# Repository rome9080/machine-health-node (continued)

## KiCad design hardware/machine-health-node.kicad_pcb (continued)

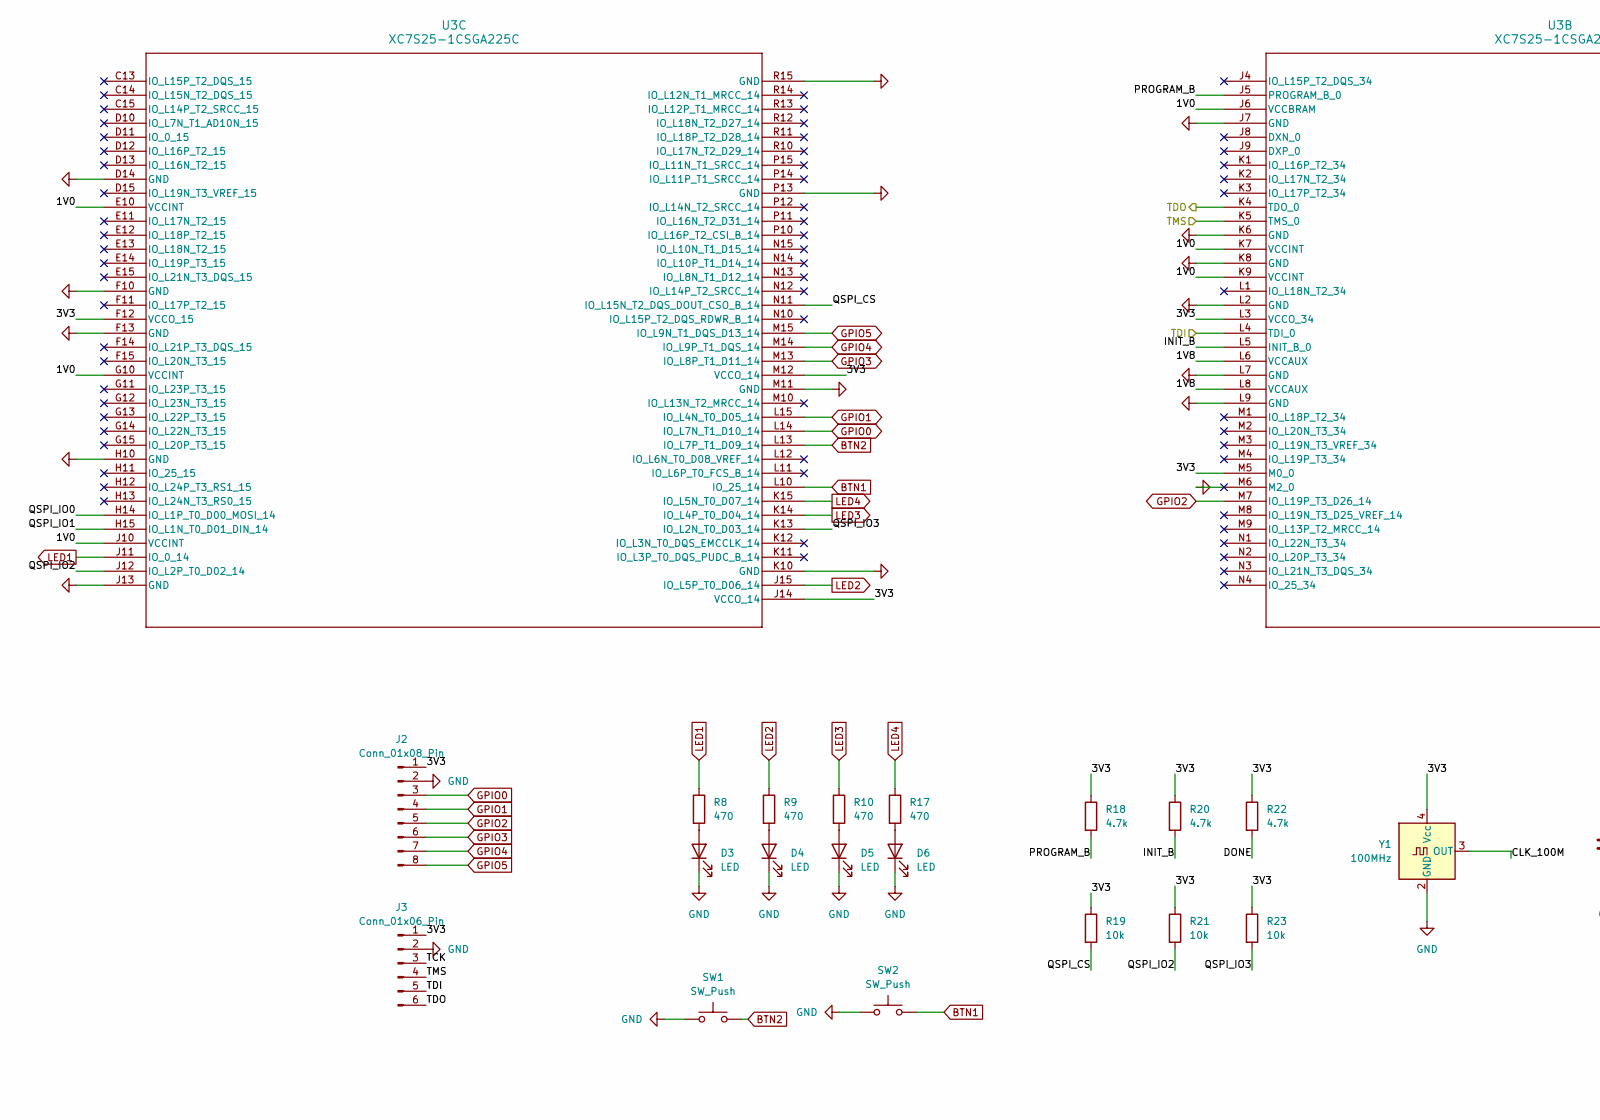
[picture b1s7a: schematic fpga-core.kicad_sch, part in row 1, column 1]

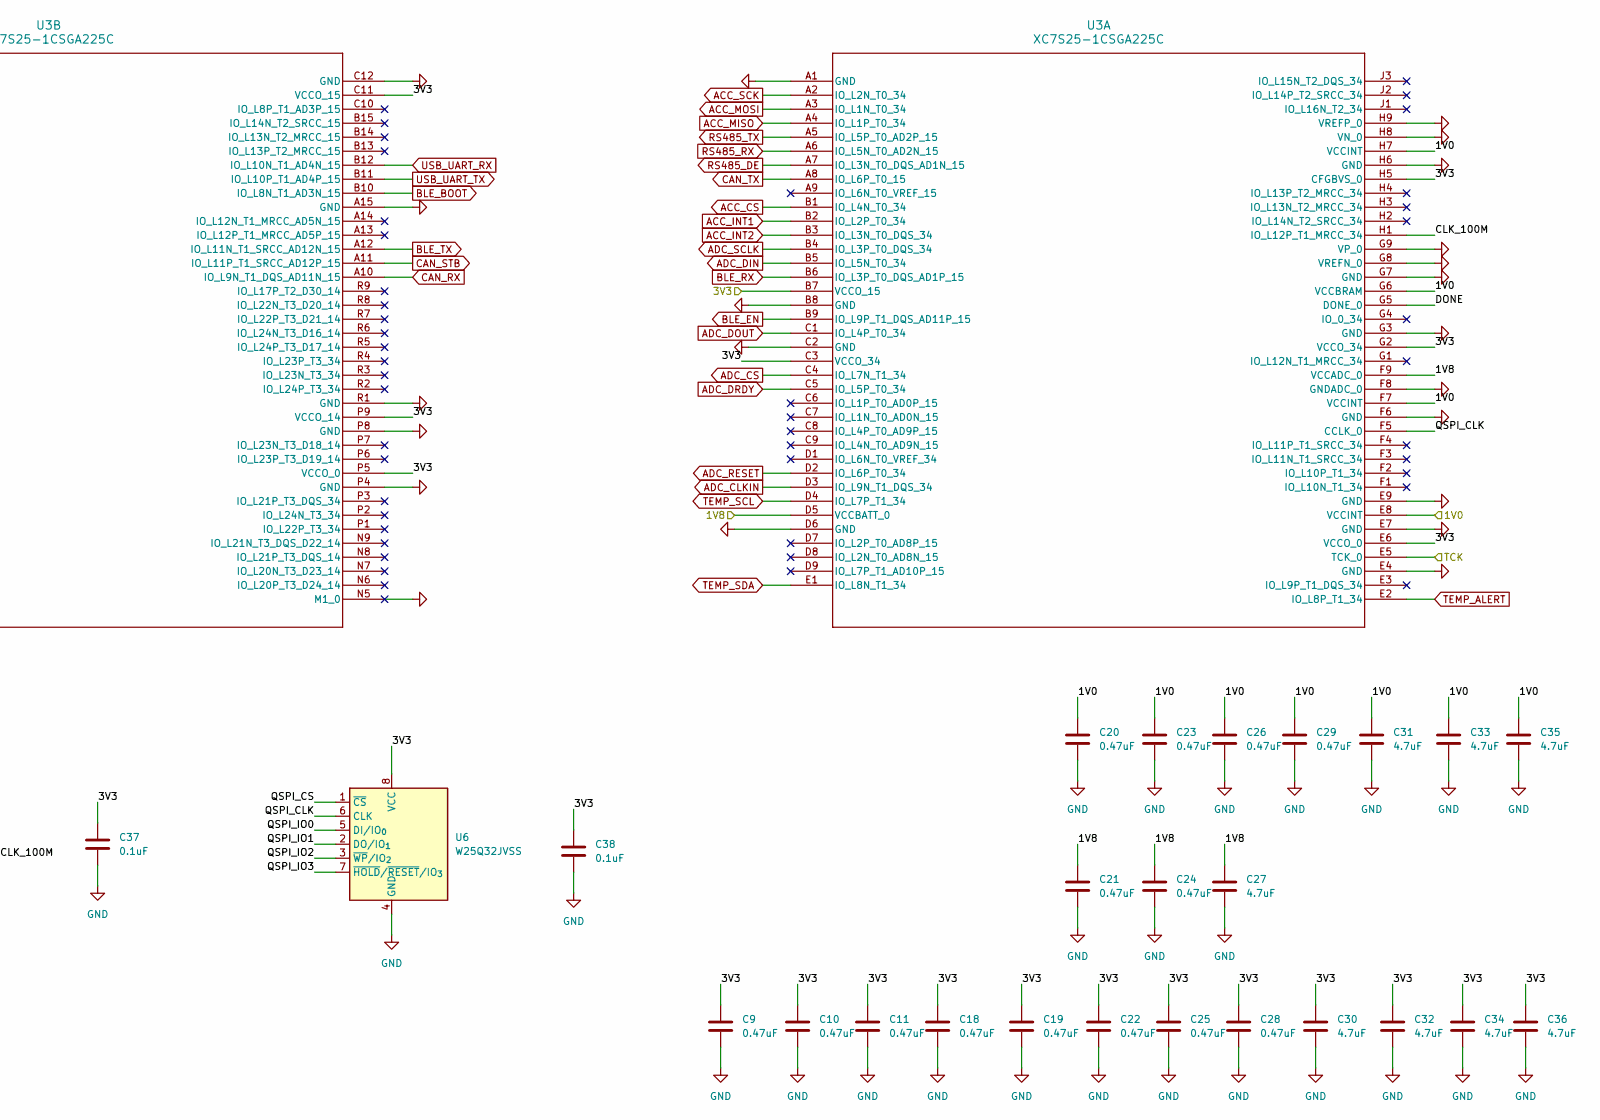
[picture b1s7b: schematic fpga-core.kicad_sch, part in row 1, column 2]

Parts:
C9, C10, C11, C18, C19, C20, C21, C22, C23, C24, C25, C26, C28, C29: 0.47uF; C_0402_1005Metric
C27, C30, C31, C32, C33, C34, C35, C36: 4.7uF; C_0603_1608Metric
C37, C38: 0.1uF; C_0402_1005Metric
D3, D4, D5, D6: LED; LED_0603_1608Metric
J2: Conn_01x08_Pin; PinHeader_1x08_P2.54mm_Vertical
J3: Conn_01x06_Pin; PinHeader_1x06_P2.54mm_Vertical
R8, R9, R10, R17: 470; R_0402_1005Metric
R18, R20, R22: 4.7k; R_0402_1005Metric
R19, R21, R23: 10k; R_0402_1005Metric
SW1, SW2: SW_Push; SW_Push_1TS009xxxx-xxxx-xxxx_6x6x5mm
U3: XC7S25-1CSGA225C; CSGA225_XIL
U6: W25Q32JVSS; SOIC-8_5.3x5.3mm_P1.27mm
Y1: 100MHz; Oscillator_SMD_Abracon_ASE-4Pin_3.2x2.5mm

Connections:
/FPGA core/CLK_100M: U3.H1 (IO_L12P_T1_MRCC_34), Y1.3 (OUT)
/FPGA core/DONE: R22.2, U3.G5 (DONE_0)
/FPGA core/INIT_B: R20.2, U3.L5 (INIT_B_0)
/FPGA core/PROGRAM_B: R18.2, U3.J5 (PROGRAM_B_0)
/FPGA core/QSPI_CLK: U3.F5 (CCLK_0), U6.6 (CLK)
/FPGA core/QSPI_CS: R19.2, U3.N11 (IO_L15N_T2_DQS_DOUT_CSO_B_14), U6.1 (~CS)
/FPGA core/QSPI_IO0: U3.H14 (IO_L1P_T0_D00_MOSI_14), U6.5 (DI/IO_{0})
/FPGA core/QSPI_IO1: U3.H15 (IO_L1N_T0_D01_DIN_14), U6.2 (DO/IO_{1})
/FPGA core/QSPI_IO2: R21.2, U3.J12 (IO_L2P_T0_D02_14), U6.3 (~WP/IO_{2})
/FPGA core/QSPI_IO3: R23.2, U3.K13 (IO_L2N_T0_D03_14), U6.7 (~HOLD/~RESET/IO_{3})
/TCK: J3.3, U3.E5 (TCK_0); also elsewhere on the board
/TDI: J3.5, U3.L4 (TDI_0); also elsewhere on the board
/TDO: J3.6, U3.K4 (TDO_0); also elsewhere on the board
/TMS: J3.4, U3.K5 (TMS_0); also elsewhere on the board
/TP_1V0: C20.1, C23.1, C26.1, C29.1, C31.1, C33.1, C35.1, U3.E8 (VCCINT), U3.E10 (VCCINT), U3.F7 (VCCINT), U3.G6 (VCCBRAM), U3.G10 (VCCINT), U3.H7 (VCCINT), U3.J6 (VCCBRAM), U3.J10 (VCCINT), U3.K7 (VCCINT), U3.K9 (VCCINT); also elsewhere on the board
/TP_1V8: C21.1, C24.1, C27.1, U3.D5 (VCCBATT_0), U3.F9 (VCCADC_0), U3.L6 (VCCAUX), U3.L8 (VCCAUX); also elsewhere on the board
/TP_3V3: C9.1, C10.1, C11.1, C18.1, C19.1, C22.1, C25.1, C28.1, C30.1, C32.1, C34.1, C36.1, C37.1, C38.1, J2.1, J3.1, R18.1, R19.1, R20.1, R21.1, R22.1, R23.1, U3.B7 (VCCO_15), U3.C3 (VCCO_34), U3.C11 (VCCO_15), U3.E6 (VCCO_0), U3.F12 (VCCO_15), U3.G2 (VCCO_34), U3.H5 (CFGBVS_0), U3.J14 (VCCO_14), U3.L3 (VCCO_34), U3.M5 (M0_0), U3.M12 (VCCO_14), U3.P5 (VCCO_0), U3.P9 (VCCO_14), U6.8 (VCC), Y1.4 (Vcc); also elsewhere on the board
ACC_CS: U3.B1 (IO_L4N_T0_34); also elsewhere on the board
ACC_INT1: U3.B2 (IO_L2P_T0_34); also elsewhere on the board
ACC_INT2: U3.B3 (IO_L3N_T0_DQS_34); also elsewhere on the board
ACC_MISO: U3.A4 (IO_L1P_T0_34); also elsewhere on the board
ACC_MOSI: U3.A3 (IO_L1N_T0_34); also elsewhere on the board
ACC_SCK: U3.A2 (IO_L2N_T0_34); also elsewhere on the board
ADC_CLKIN: U3.D3 (IO_L9N_T1_DQS_34); also elsewhere on the board
ADC_CS: U3.C4 (IO_L7N_T1_34); also elsewhere on the board
ADC_DIN: U3.B5 (IO_L5N_T0_34); also elsewhere on the board
ADC_DOUT: U3.C1 (IO_L4P_T0_34); also elsewhere on the board
ADC_DRDY: U3.C5 (IO_L5P_T0_34); also elsewhere on the board
ADC_RESET: U3.D2 (IO_L6P_T0_34); also elsewhere on the board
ADC_SCLK: U3.B4 (IO_L3P_T0_DQS_34); also elsewhere on the board
BLE_BOOT: U3.B10 (IO_L8N_T1_AD3N_15); also elsewhere on the board
BLE_EN: U3.B9 (IO_L9P_T1_DQS_AD11P_15); also elsewhere on the board
BLE_RX: U3.B6 (IO_L3P_T0_DQS_AD1P_15); also elsewhere on the board
BLE_TX: U3.A12 (IO_L11N_T1_SRCC_AD12N_15); also elsewhere on the board
BTN1: SW2.2, U3.L10 (IO_25_14)
BTN2: SW1.2, U3.L13 (IO_L7P_T1_D09_14)
CAN_RX: U3.A10 (IO_L9N_T1_DQS_AD11N_15); also elsewhere on the board
CAN_STB: U3.A11 (IO_L11P_T1_SRCC_AD12P_15); also elsewhere on the board
CAN_TX: U3.A8 (IO_L6P_T0_15); also elsewhere on the board
GND: C9.2, C10.2, C11.2, C18.2, C19.2, C20.2, C21.2, C22.2, C23.2, C24.2, C25.2, C26.2, C27.2, C28.2, C29.2, C30.2, C31.2, C32.2, C33.2, C34.2, C35.2, C36.2, C37.2, C38.2, D3.1 (K), D4.1 (K), D5.1 (K), D6.1 (K), J2.2, J3.2, SW1.1, SW2.1, U3.A1 (GND), U3.A15 (GND), U3.B8 (GND), U3.C2 (GND), U3.C12 (GND), U3.D6 (GND), U3.D14 (GND), U3.E4 (GND), U3.E7 (GND), U3.E9 (GND), U3.F6 (GND), U3.F8 (GNDADC_0), U3.F10 (GND), U3.F13 (GND), U3.G3 (GND), U3.G7 (GND), U3.G8 (VREFN_0), U3.G9 (VP_0), U3.H6 (GND), U3.H8 (VN_0), U3.H9 (VREFP_0), U3.H10 (GND), U3.J7 (GND), U3.J13 (GND), U3.K6 (GND), U3.K8 (GND), U3.K10 (GND), U3.L2 (GND), U3.L7 (GND), U3.L9 (GND), U3.M6 (M2_0), U3.M11 (GND), U3.N5 (M1_0), U3.P4 (GND), U3.P8 (GND), U3.P13 (GND), U3.R1 (GND), U3.R15 (GND), U6.4 (GND), Y1.2 (GND); also elsewhere on the board
GPIO0: J2.3, U3.L14 (IO_L7N_T1_D10_14)
GPIO1: J2.4, U3.L15 (IO_L4N_T0_D05_14)
GPIO2: J2.5, U3.M7 (IO_L19P_T3_D26_14)
GPIO3: J2.6, U3.M13 (IO_L8P_T1_D11_14)
GPIO4: J2.7, U3.M14 (IO_L9P_T1_DQS_14)
GPIO5: J2.8, U3.M15 (IO_L9N_T1_DQS_D13_14)
LED1: R8.1, U3.J11 (IO_0_14)
LED2: R9.1, U3.J15 (IO_L5P_T0_D06_14)
LED3: R10.1, U3.K14 (IO_L4P_T0_D04_14)
LED4: R17.1, U3.K15 (IO_L5N_T0_D07_14)
unnamed: D3.2 (A), R8.2
unnamed: D4.2 (A), R9.2
unnamed: D5.2 (A), R10.2
unnamed: D6.2 (A), R17.2
RS485_DE: U3.A7 (IO_L3N_T0_DQS_AD1N_15); also elsewhere on the board
RS485_RX: U3.A6 (IO_L5N_T0_AD2N_15); also elsewhere on the board
RS485_TX: U3.A5 (IO_L5P_T0_AD2P_15); also elsewhere on the board
TEMP_ALERT: U3.E2 (IO_L8P_T1_34); also elsewhere on the board
TEMP_SCL: U3.D4 (IO_L7P_T1_34); also elsewhere on the board
TEMP_SDA: U3.E1 (IO_L8N_T1_34); also elsewhere on the board
USB_UART_RX: U3.B12 (IO_L10N_T1_AD4N_15); also elsewhere on the board
USB_UART_TX: U3.B11 (IO_L10P_T1_AD4P_15); also elsewhere on the board

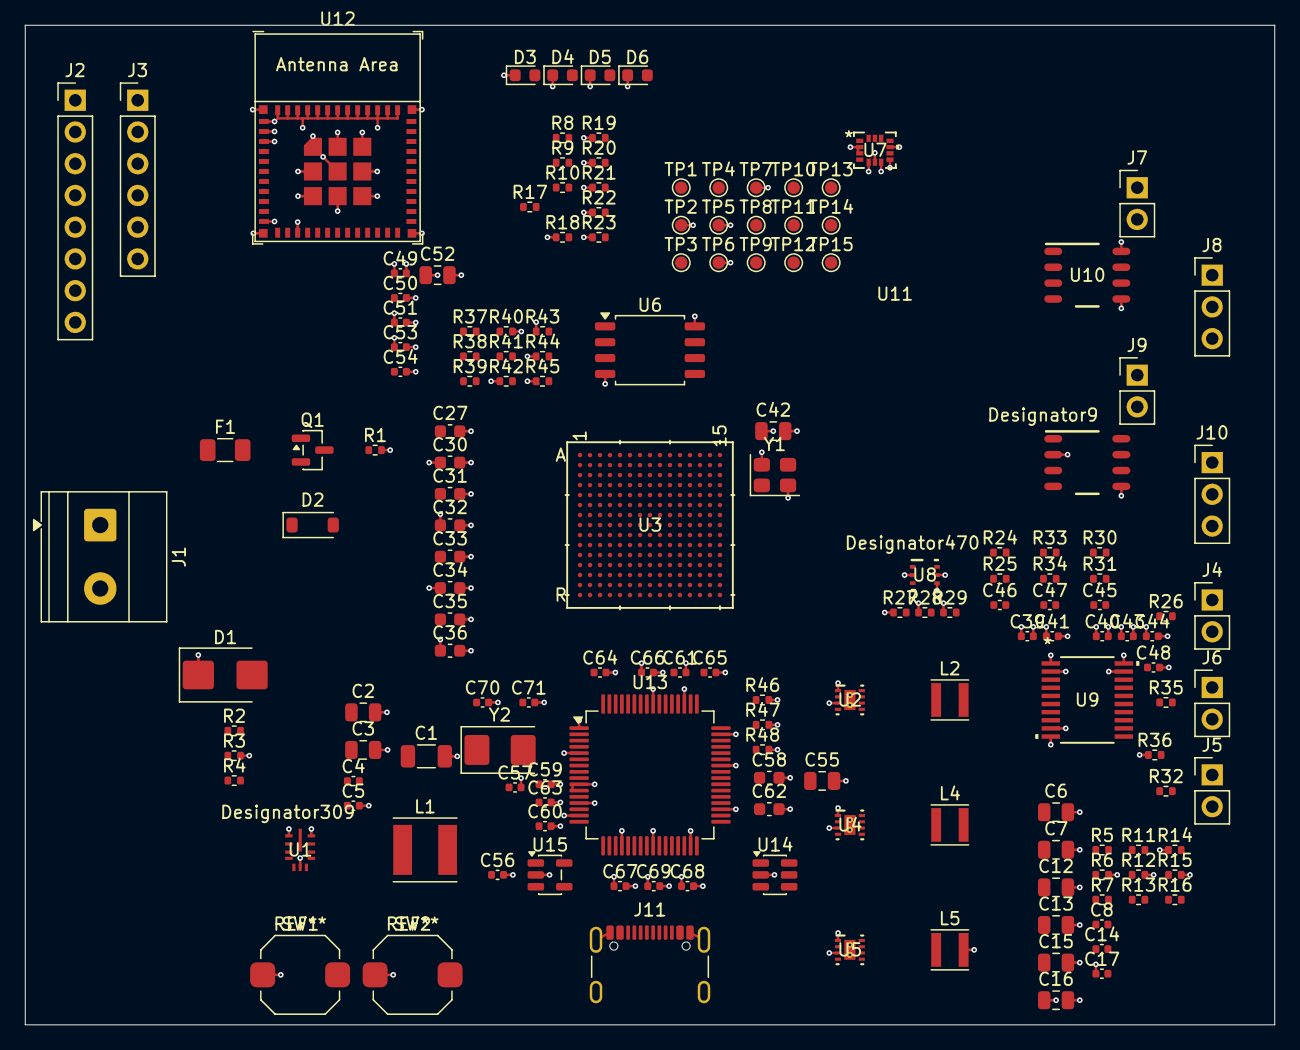
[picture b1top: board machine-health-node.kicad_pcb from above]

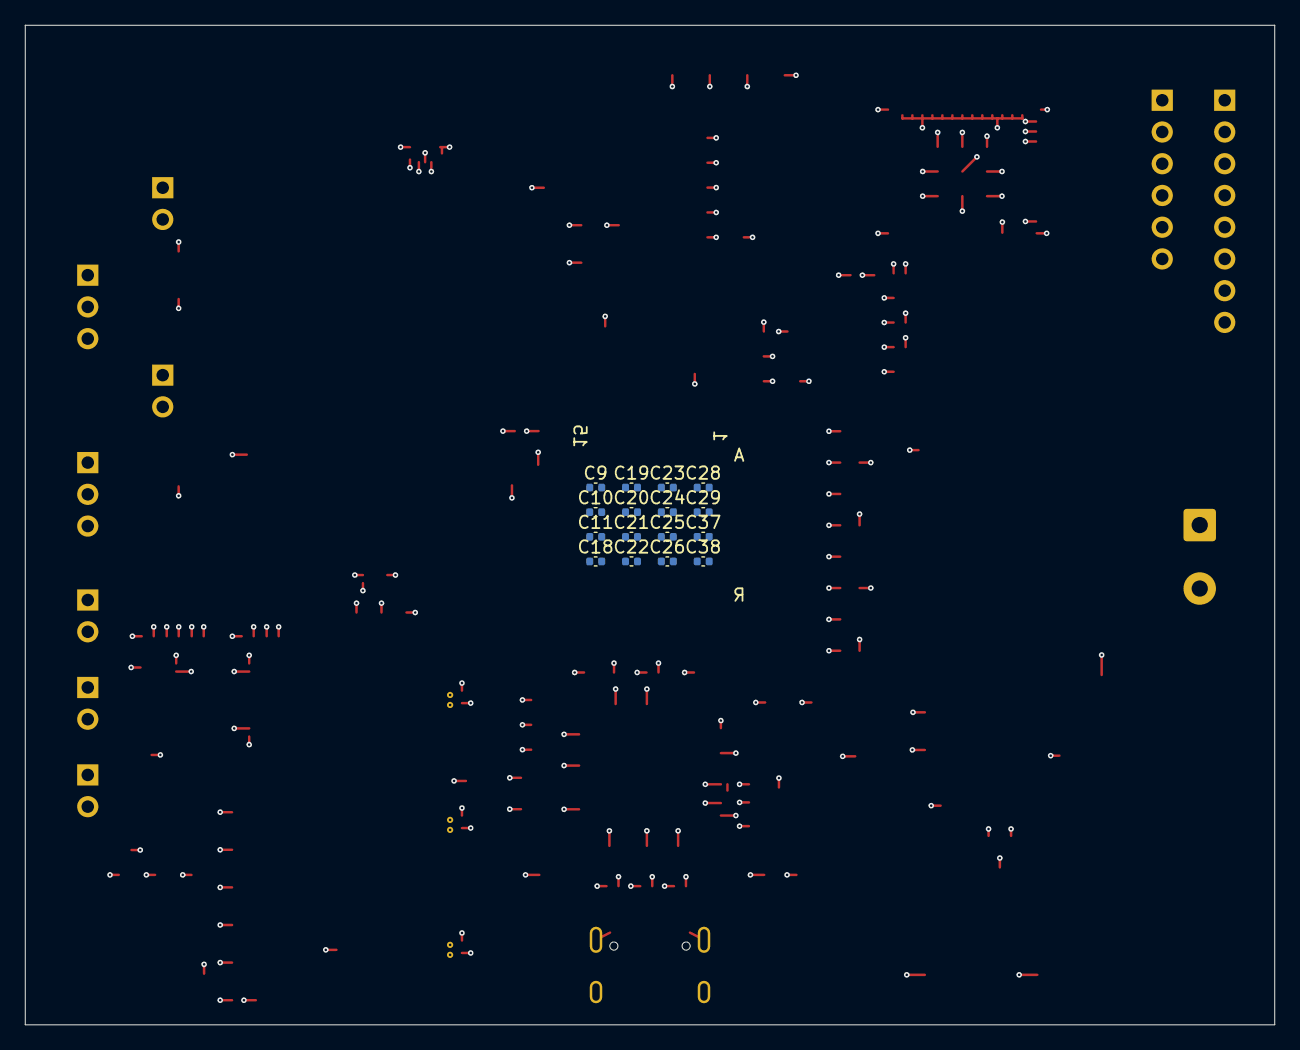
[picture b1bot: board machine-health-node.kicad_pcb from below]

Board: 4 copper layers, 100.0 x 80.0 mm, 176 parts (16 on the bottom side), 116 nets.
